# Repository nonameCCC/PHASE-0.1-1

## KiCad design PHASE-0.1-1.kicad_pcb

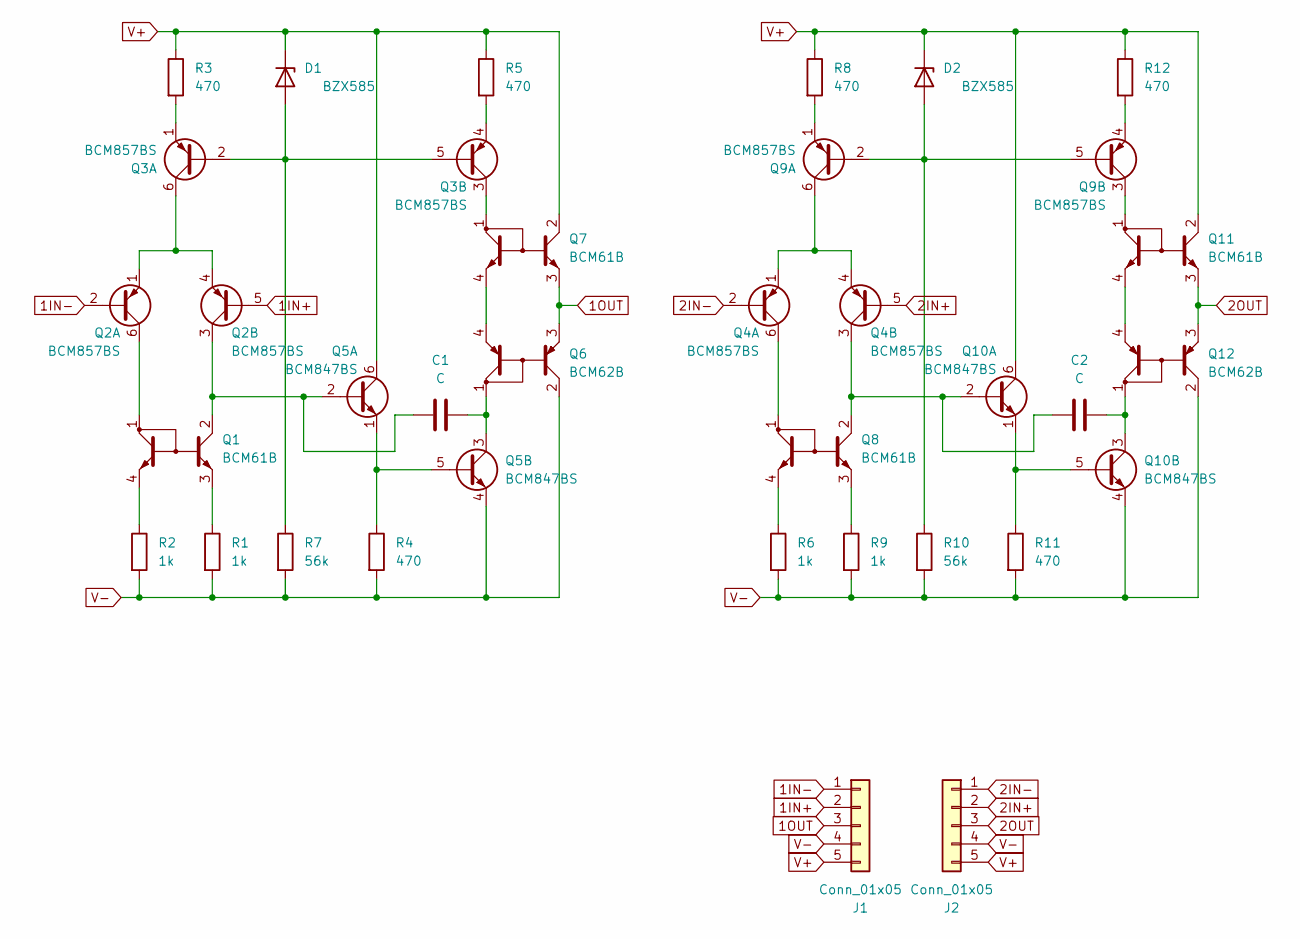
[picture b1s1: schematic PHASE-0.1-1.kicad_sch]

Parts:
C1, C2: C; C_0402_1005Metric
D1, D2: BZX585; D_SOD-523
J1, J2: Conn_01x05; PinHeader_1x05_P1.27mm_Vertical
Q1, Q7, Q8, Q11: BCM61B; SOT-143
Q2, Q3, Q4, Q9: BCM857BS; SOT-363_SC-70-6
Q5, Q10: BCM847BS; SOT-363_SC-70-6
Q6, Q12: BCM62B; SOT-143
R1, R2, R6, R9: 1k; R_0402_1005Metric
R3, R4, R5, R8, R11, R12: 470; R_0402_1005Metric
R7, R10: 56k; R_0402_1005Metric

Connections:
1IN+: J1.2, Q2.5 (B2)
1IN-: J1.1, Q2.2 (B1)
1OUT: J1.3, Q6.3 (E1), Q7.3 (E1)
2IN+: J2.2, Q4.5 (B2)
2IN-: J2.1, Q4.2 (B1)
2OUT: J2.3, Q11.3 (E1), Q12.3 (E1)
unnamed: D1.2 (A), Q3.2 (B1), Q3.5 (B2), R7.1
unnamed: D2.2 (A), Q9.2 (B1), Q9.5 (B2), R10.1
unnamed: C1.1, Q1.2 (C1), Q2.3 (C2), Q5.2 (B1)
unnamed: Q1.1 (C2), Q2.6 (C1)
unnamed: Q1.3 (E1), R1.1
unnamed: Q1.4 (E2), R2.1
unnamed: Q2.1 (E1), Q2.4 (E2), Q3.6 (C1)
unnamed: Q3.1 (E1), R3.2
unnamed: Q3.3 (C2), Q7.1 (C2)
unnamed: Q3.4 (E2), R5.2
unnamed: Q4.6 (C1), Q8.1 (C2)
unnamed: Q4.1 (E1), Q4.4 (E2), Q9.6 (C1)
unnamed: Q5.1 (E1), Q5.5 (B2), R4.1
unnamed: C1.2, Q5.3 (C2), Q6.1 (C2)
unnamed: Q6.4 (E2), Q7.4 (E2)
unnamed: Q8.3 (E1), R9.1
unnamed: Q8.4 (E2), R6.1
unnamed: Q9.1 (E1), R8.2
unnamed: Q9.4 (E2), R12.2
unnamed: C2.1, Q4.3 (C2), Q8.2 (C1), Q10.2 (B1)
unnamed: Q10.1 (E1), Q10.5 (B2), R11.1
unnamed: C2.2, Q10.3 (C2), Q12.1 (C2)
unnamed: Q9.3 (C2), Q11.1 (C2)
unnamed: Q11.4 (E2), Q12.4 (E2)
V+: D1.1 (K), D2.1 (K), J1.5, J2.5, Q5.6 (C1), Q7.2 (C1), Q10.6 (C1), Q11.2 (C1), R3.1, R5.1, R8.1, R12.1
V-: J1.4, J2.4, Q5.4 (E2), Q6.2 (C1), Q10.4 (E2), Q12.2 (C1), R1.2, R2.2, R4.2, R6.2, R7.2, R9.2, R10.2, R11.2

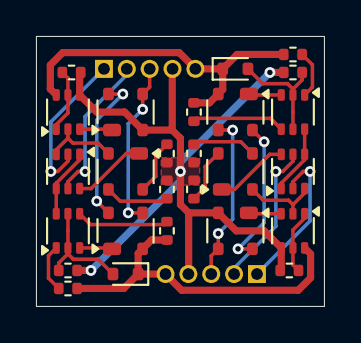
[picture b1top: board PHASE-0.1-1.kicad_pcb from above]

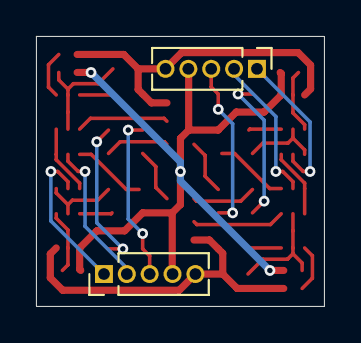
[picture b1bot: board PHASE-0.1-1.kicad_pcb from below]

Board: 2 copper layers, 16.0 x 15.0 mm, 28 parts (2 on the bottom side), 32 nets.

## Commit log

2025-09-03 Move SPICE Models to A New Folder
